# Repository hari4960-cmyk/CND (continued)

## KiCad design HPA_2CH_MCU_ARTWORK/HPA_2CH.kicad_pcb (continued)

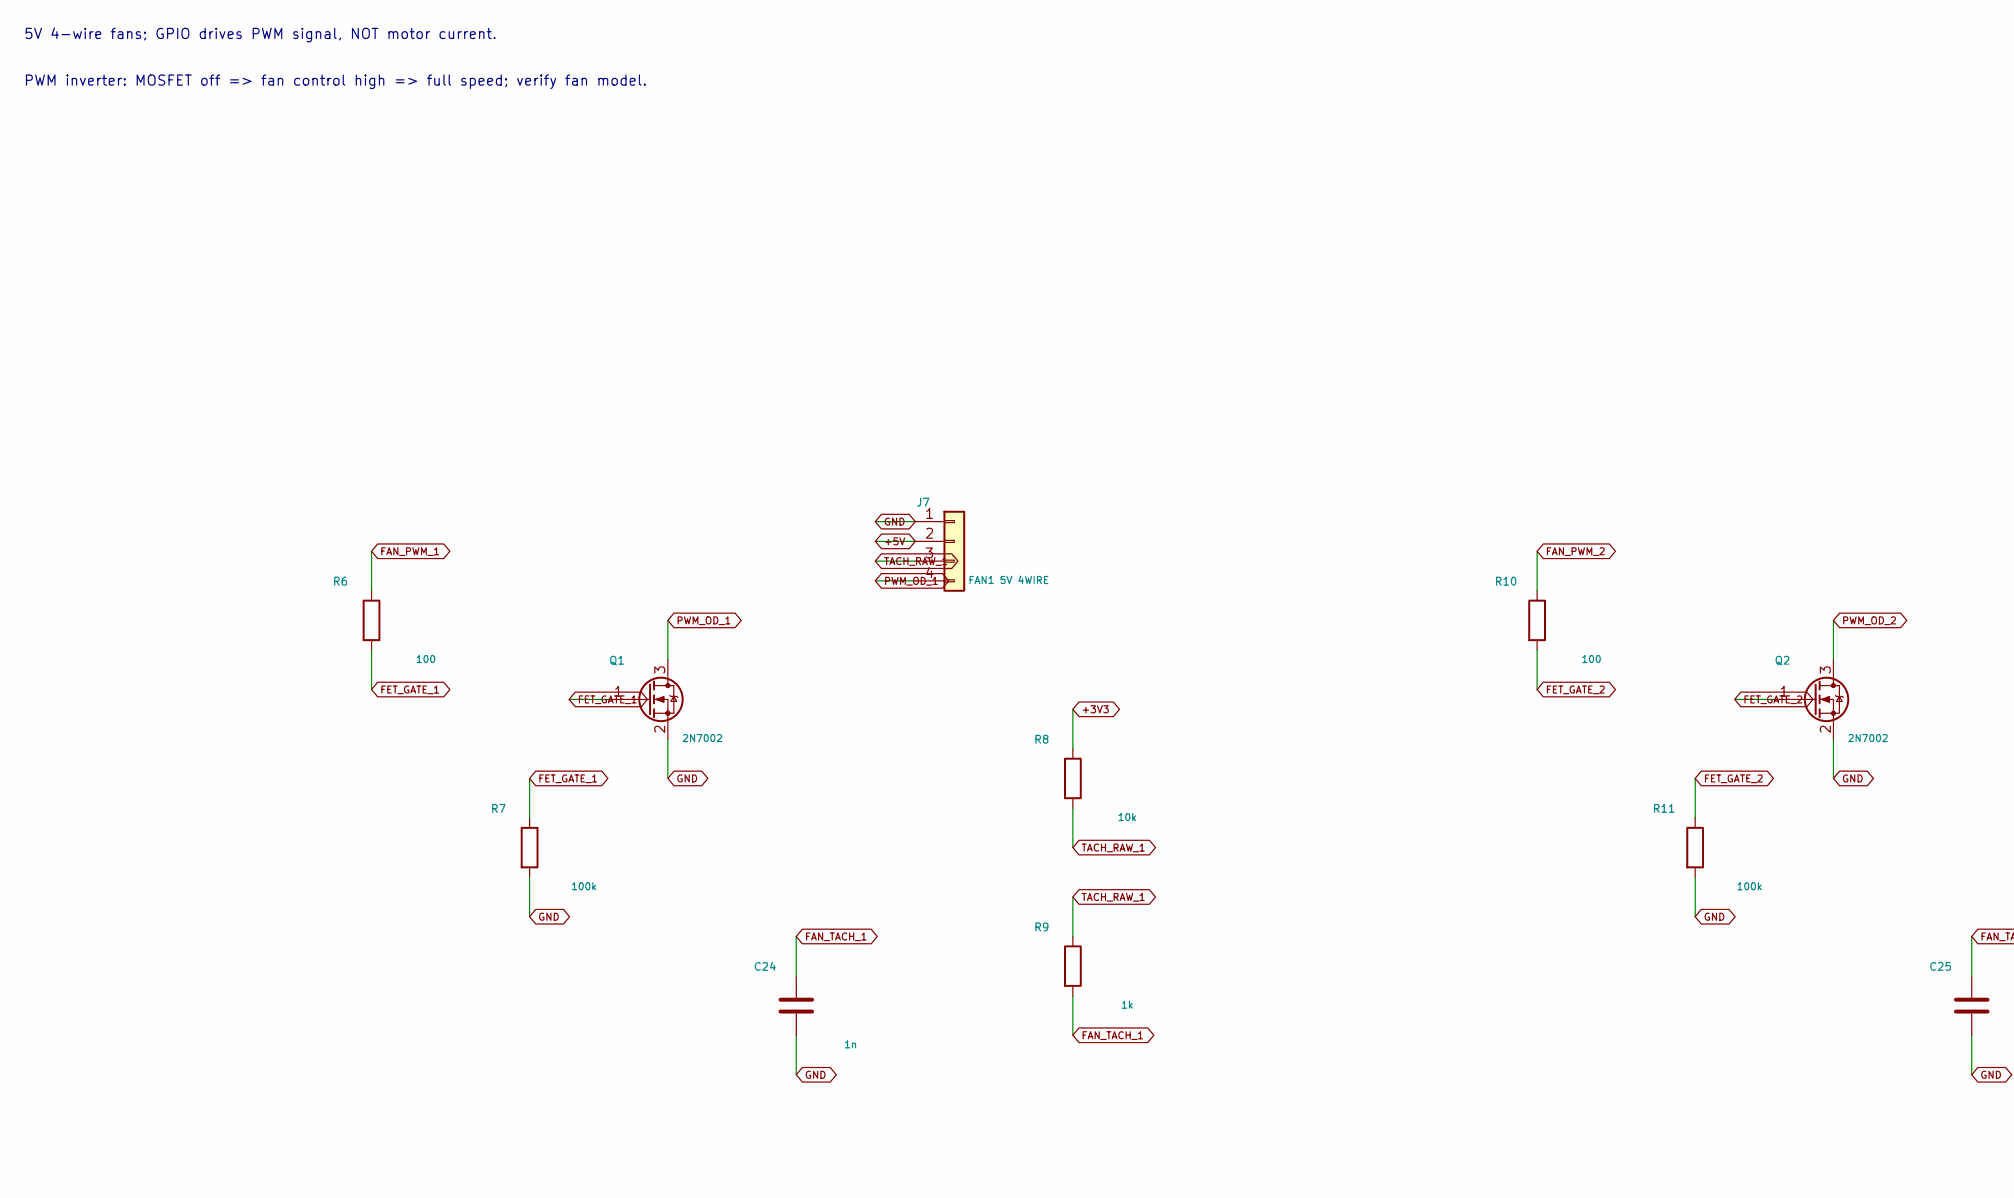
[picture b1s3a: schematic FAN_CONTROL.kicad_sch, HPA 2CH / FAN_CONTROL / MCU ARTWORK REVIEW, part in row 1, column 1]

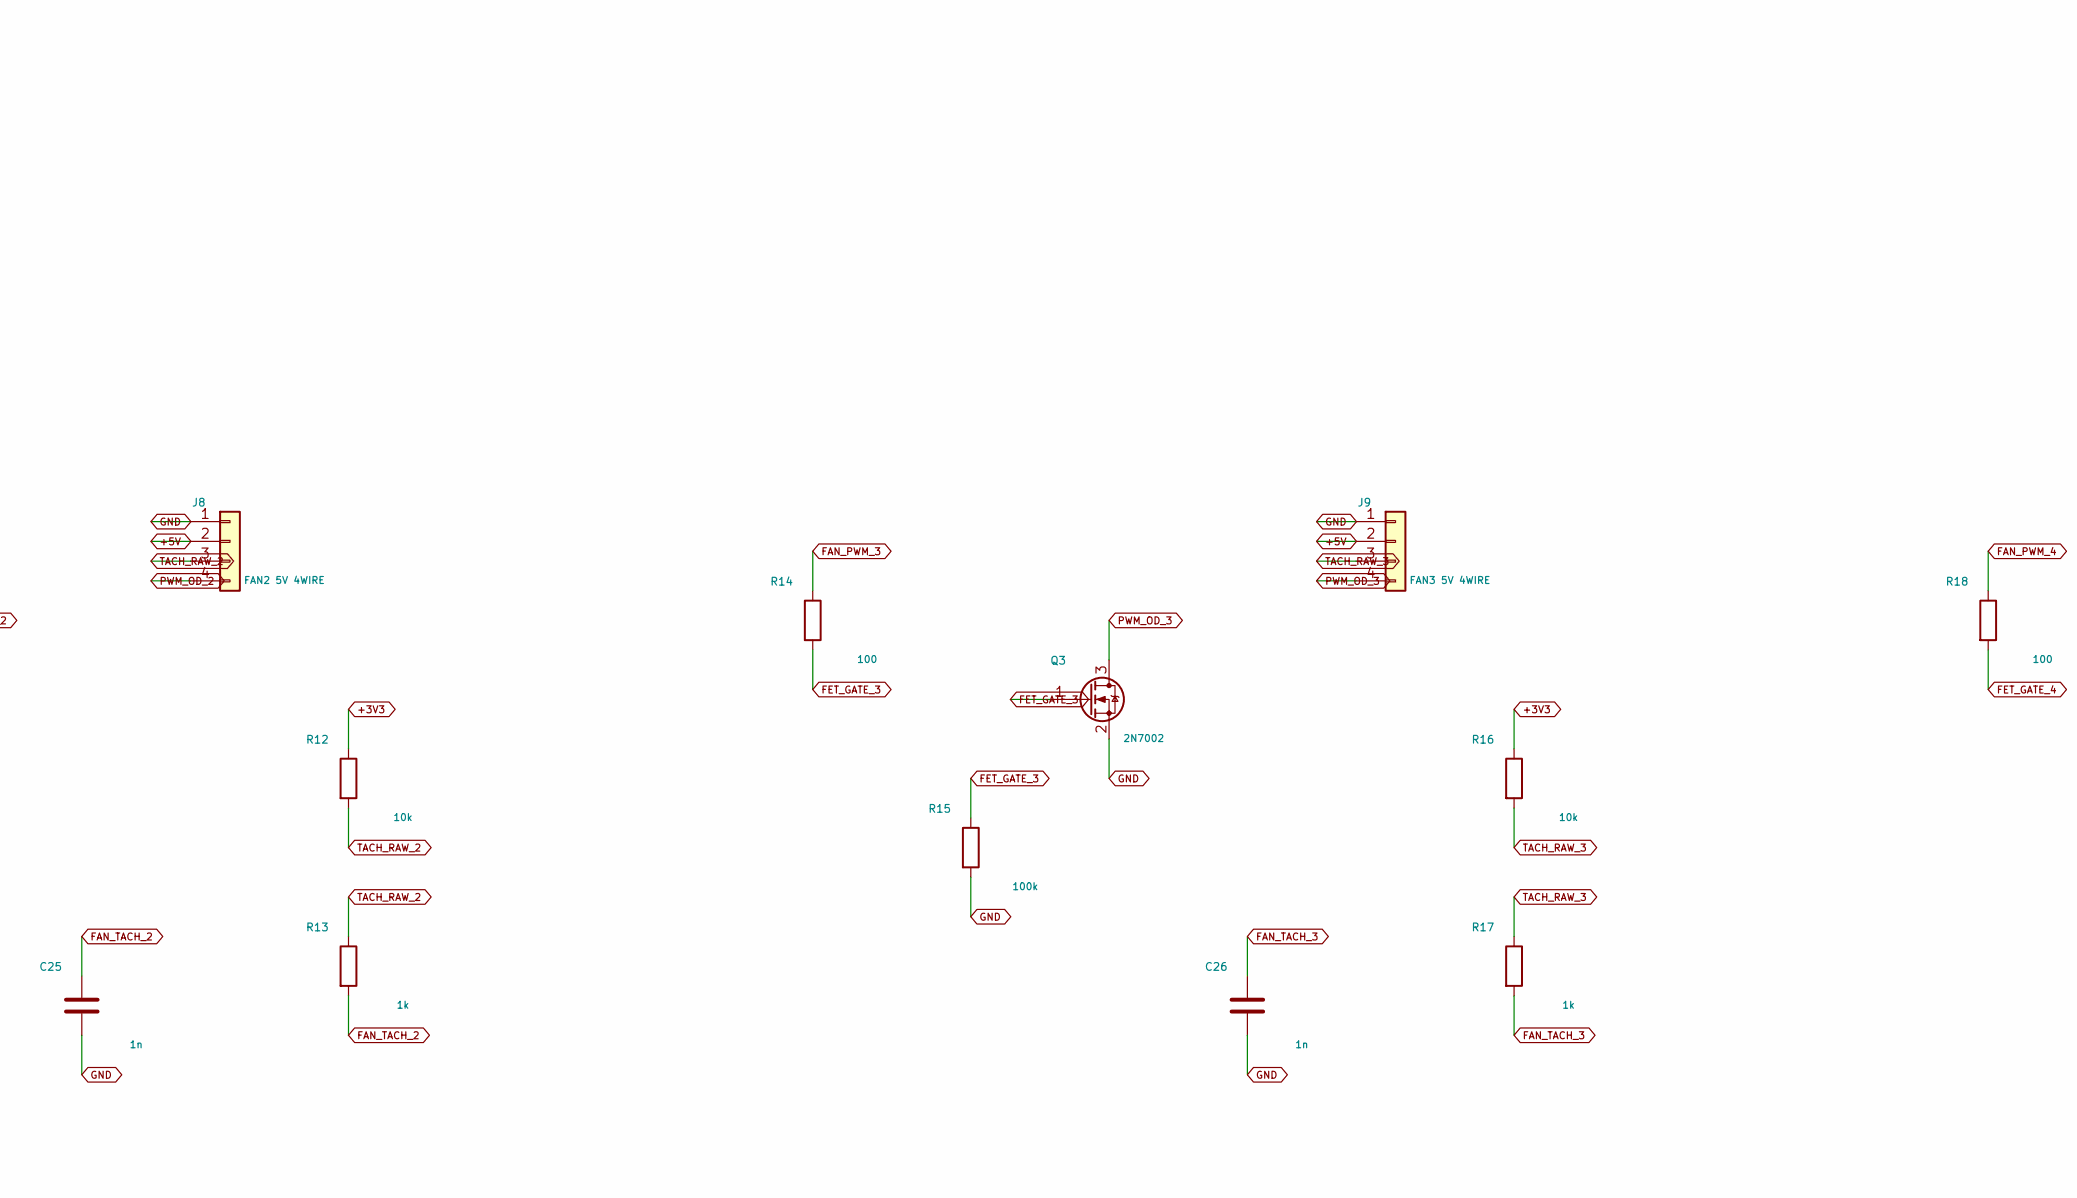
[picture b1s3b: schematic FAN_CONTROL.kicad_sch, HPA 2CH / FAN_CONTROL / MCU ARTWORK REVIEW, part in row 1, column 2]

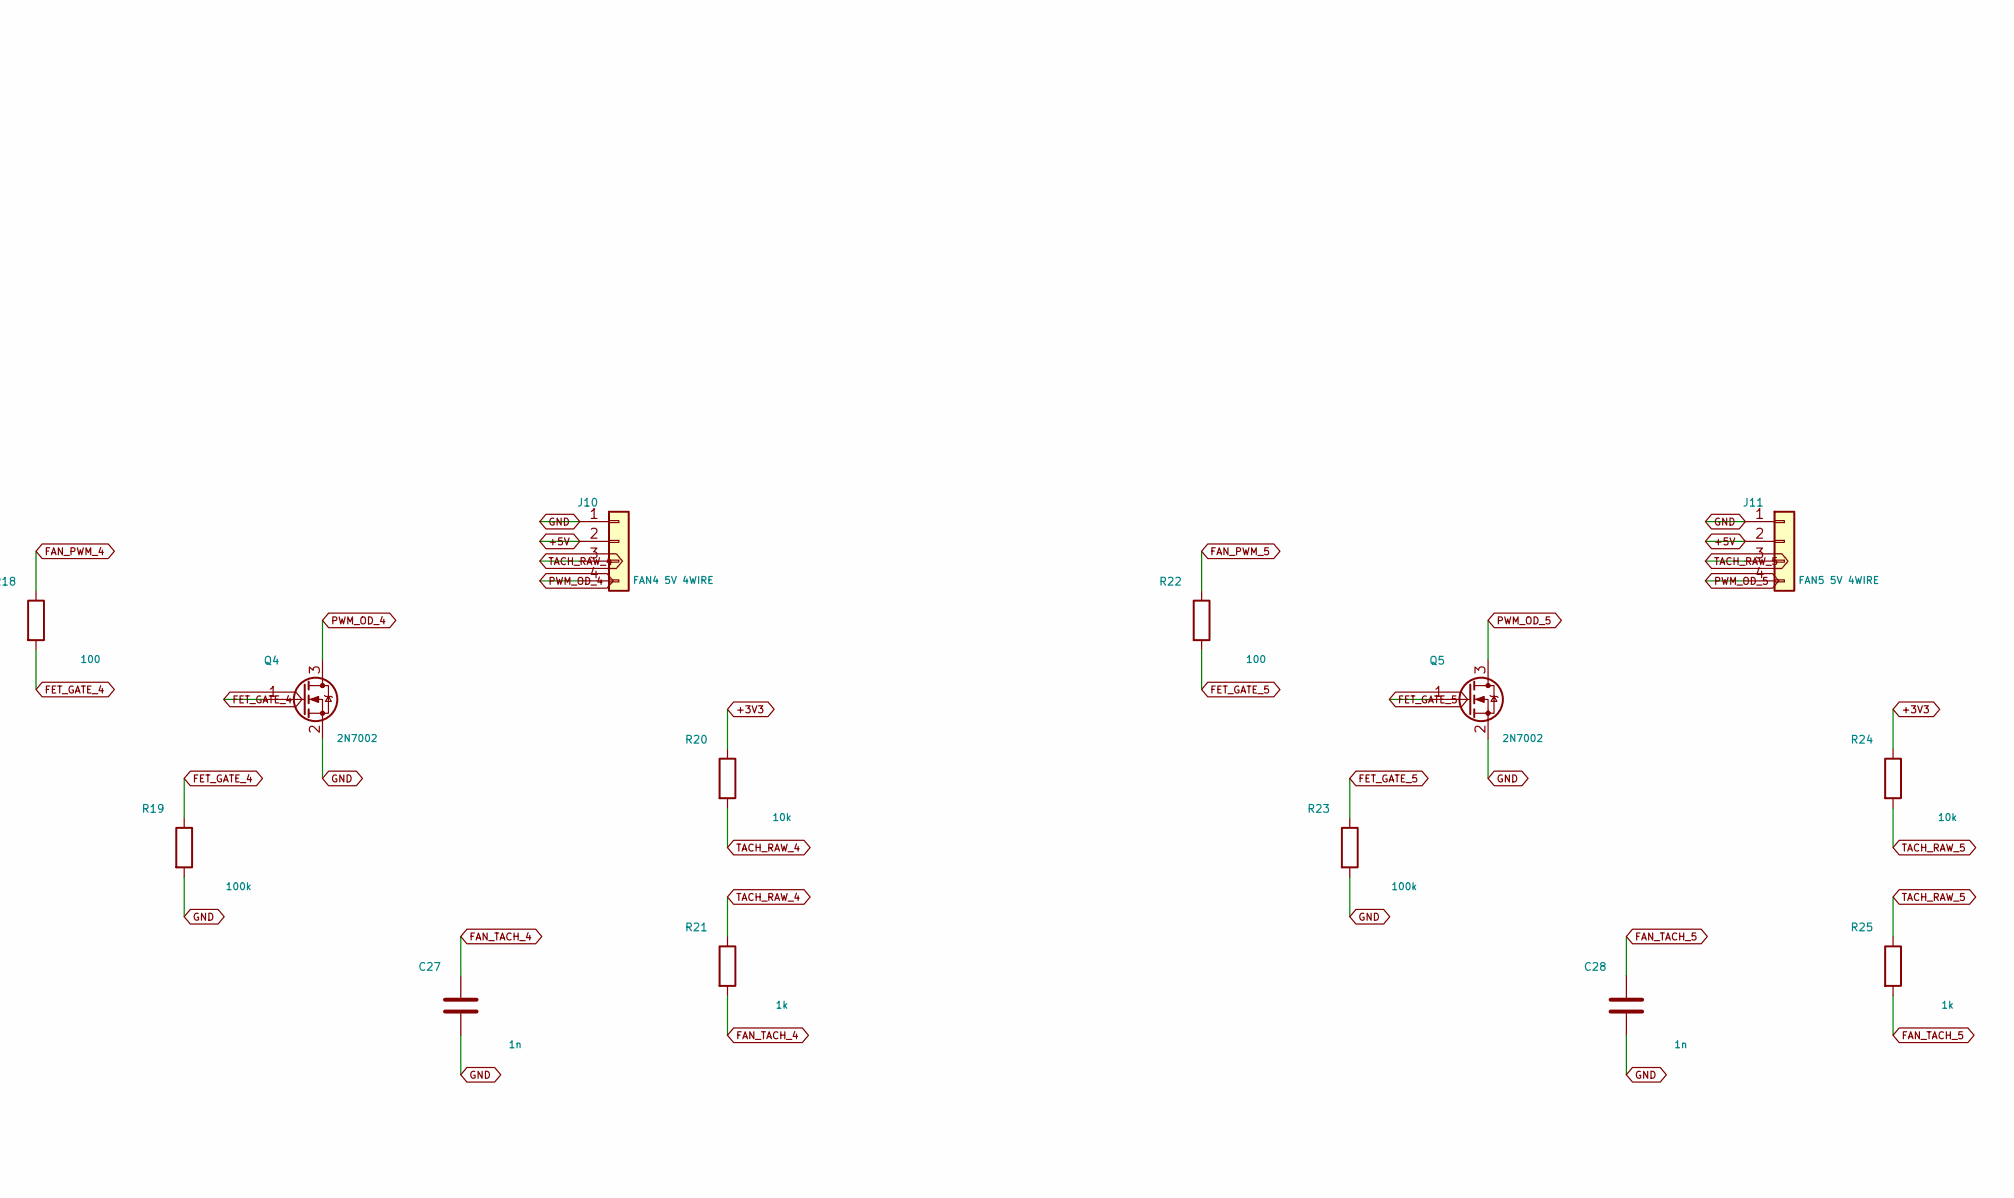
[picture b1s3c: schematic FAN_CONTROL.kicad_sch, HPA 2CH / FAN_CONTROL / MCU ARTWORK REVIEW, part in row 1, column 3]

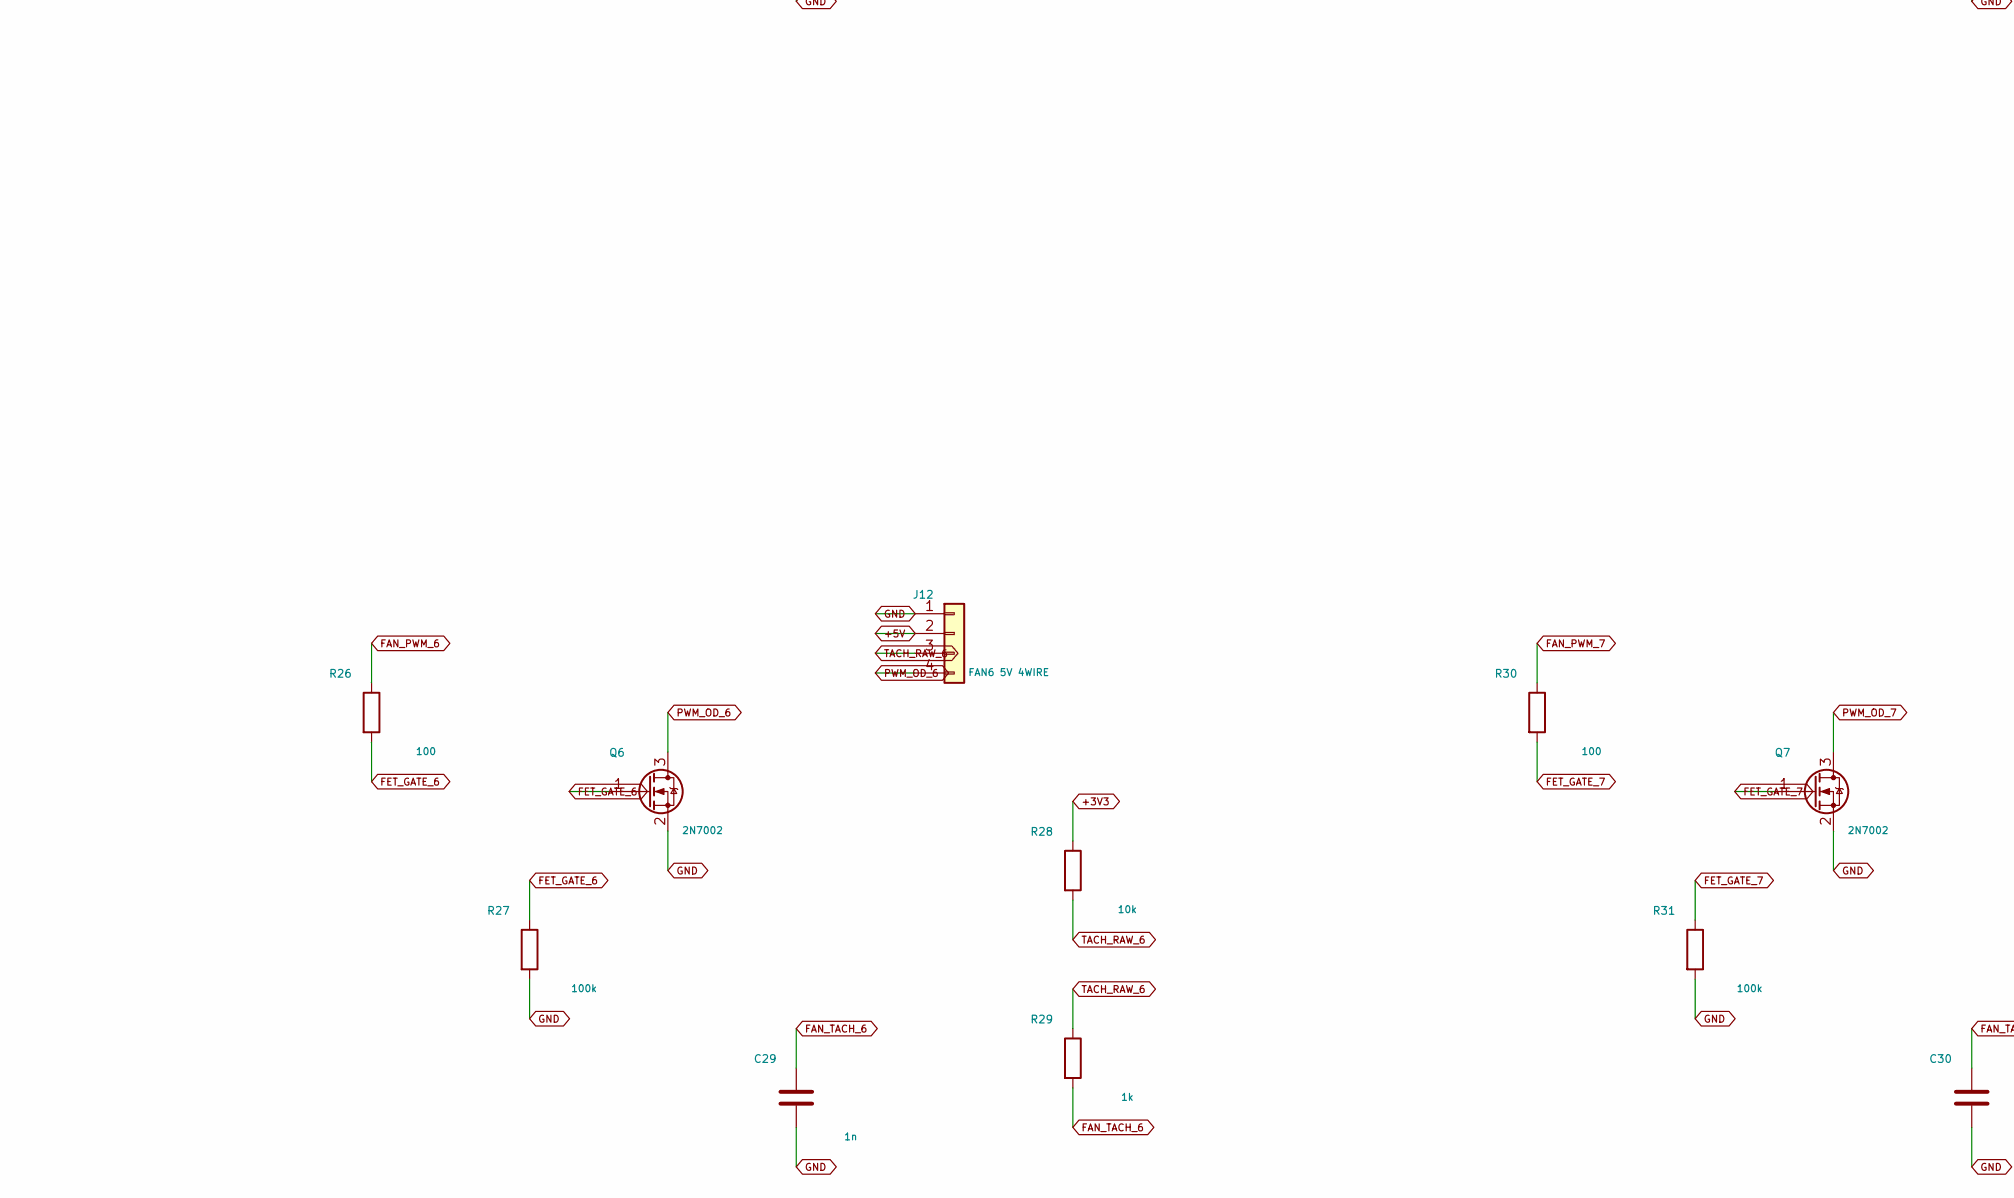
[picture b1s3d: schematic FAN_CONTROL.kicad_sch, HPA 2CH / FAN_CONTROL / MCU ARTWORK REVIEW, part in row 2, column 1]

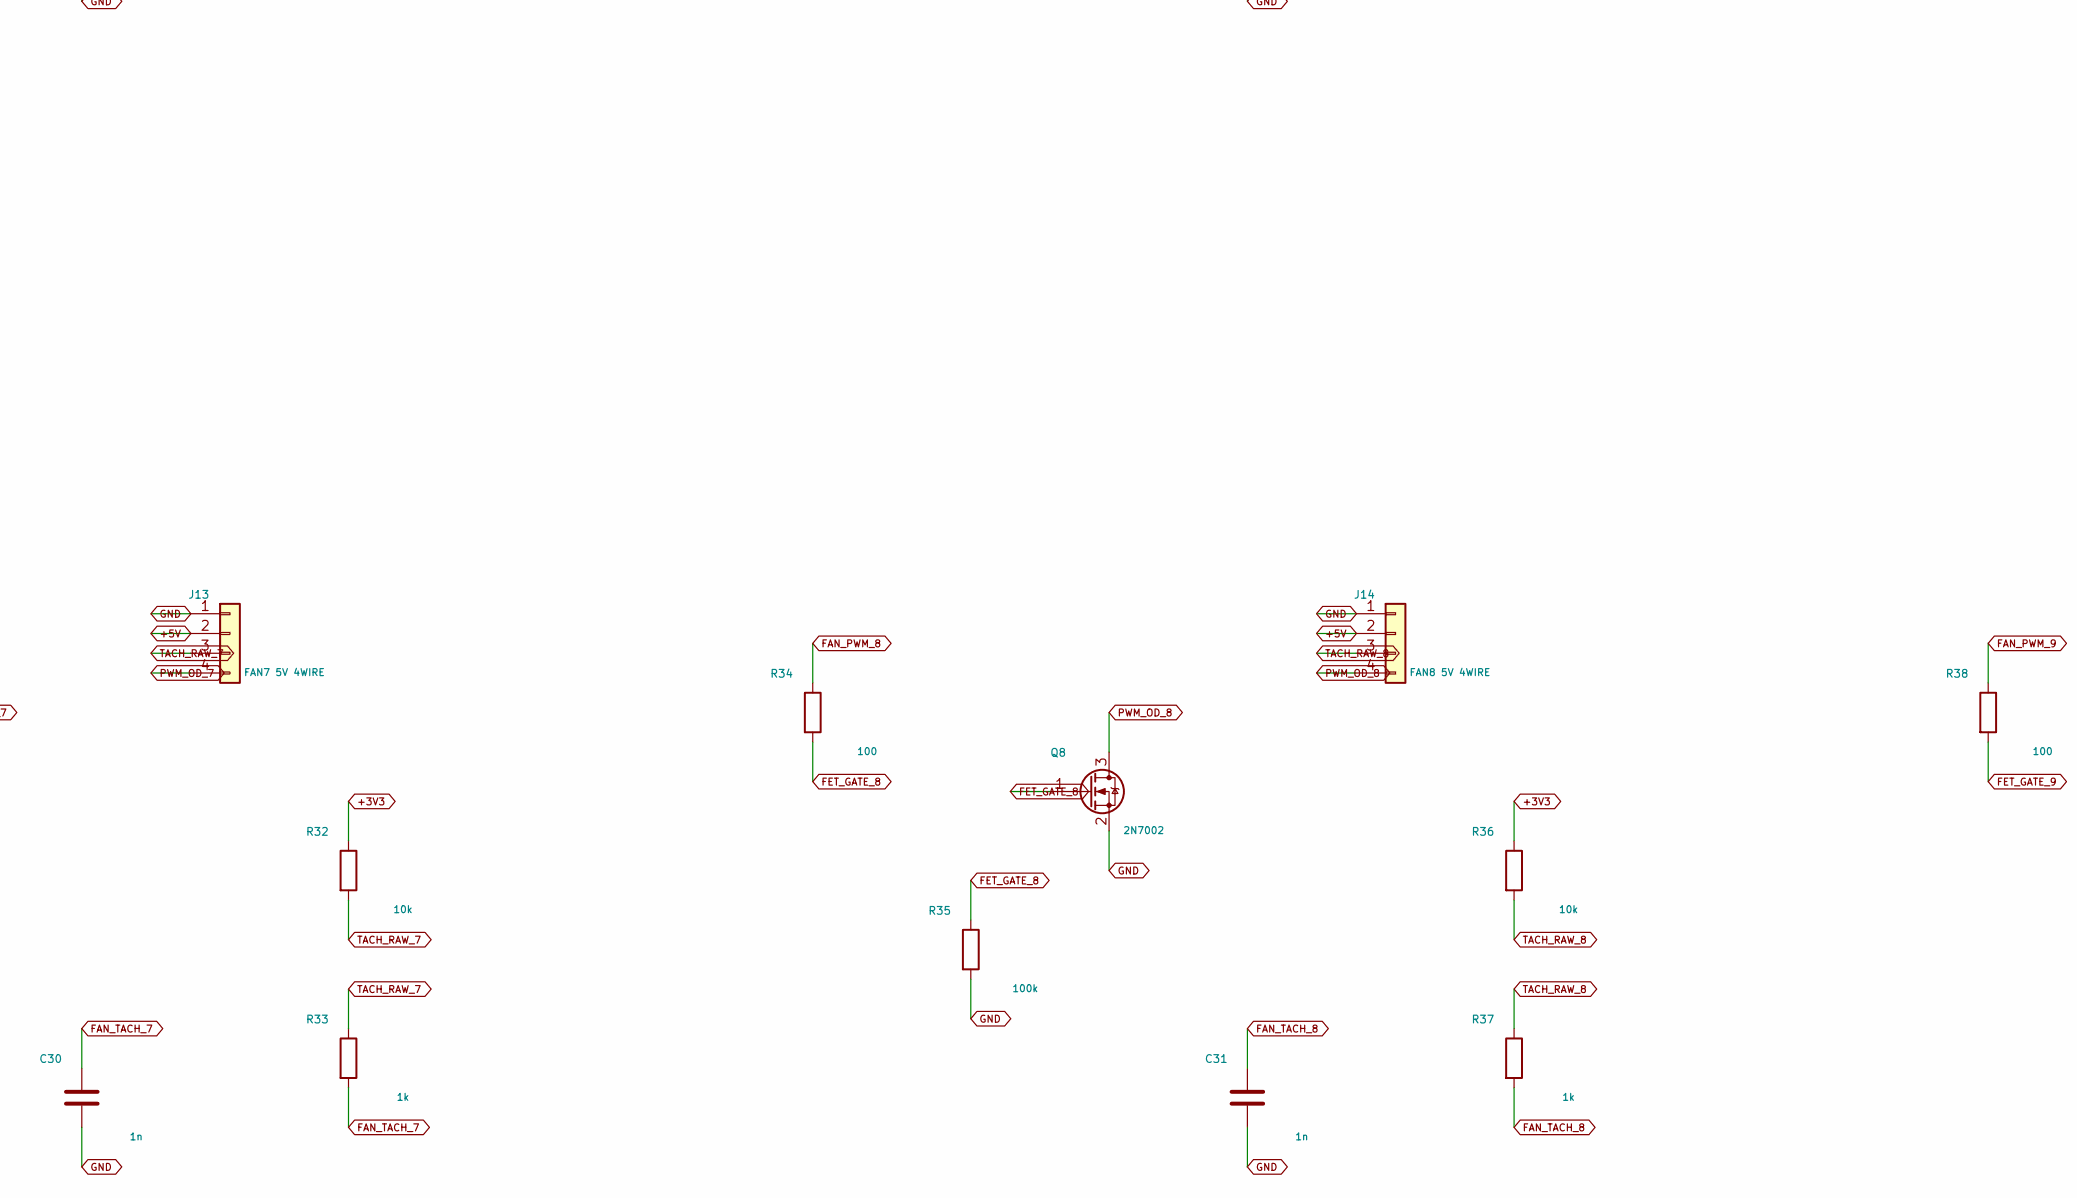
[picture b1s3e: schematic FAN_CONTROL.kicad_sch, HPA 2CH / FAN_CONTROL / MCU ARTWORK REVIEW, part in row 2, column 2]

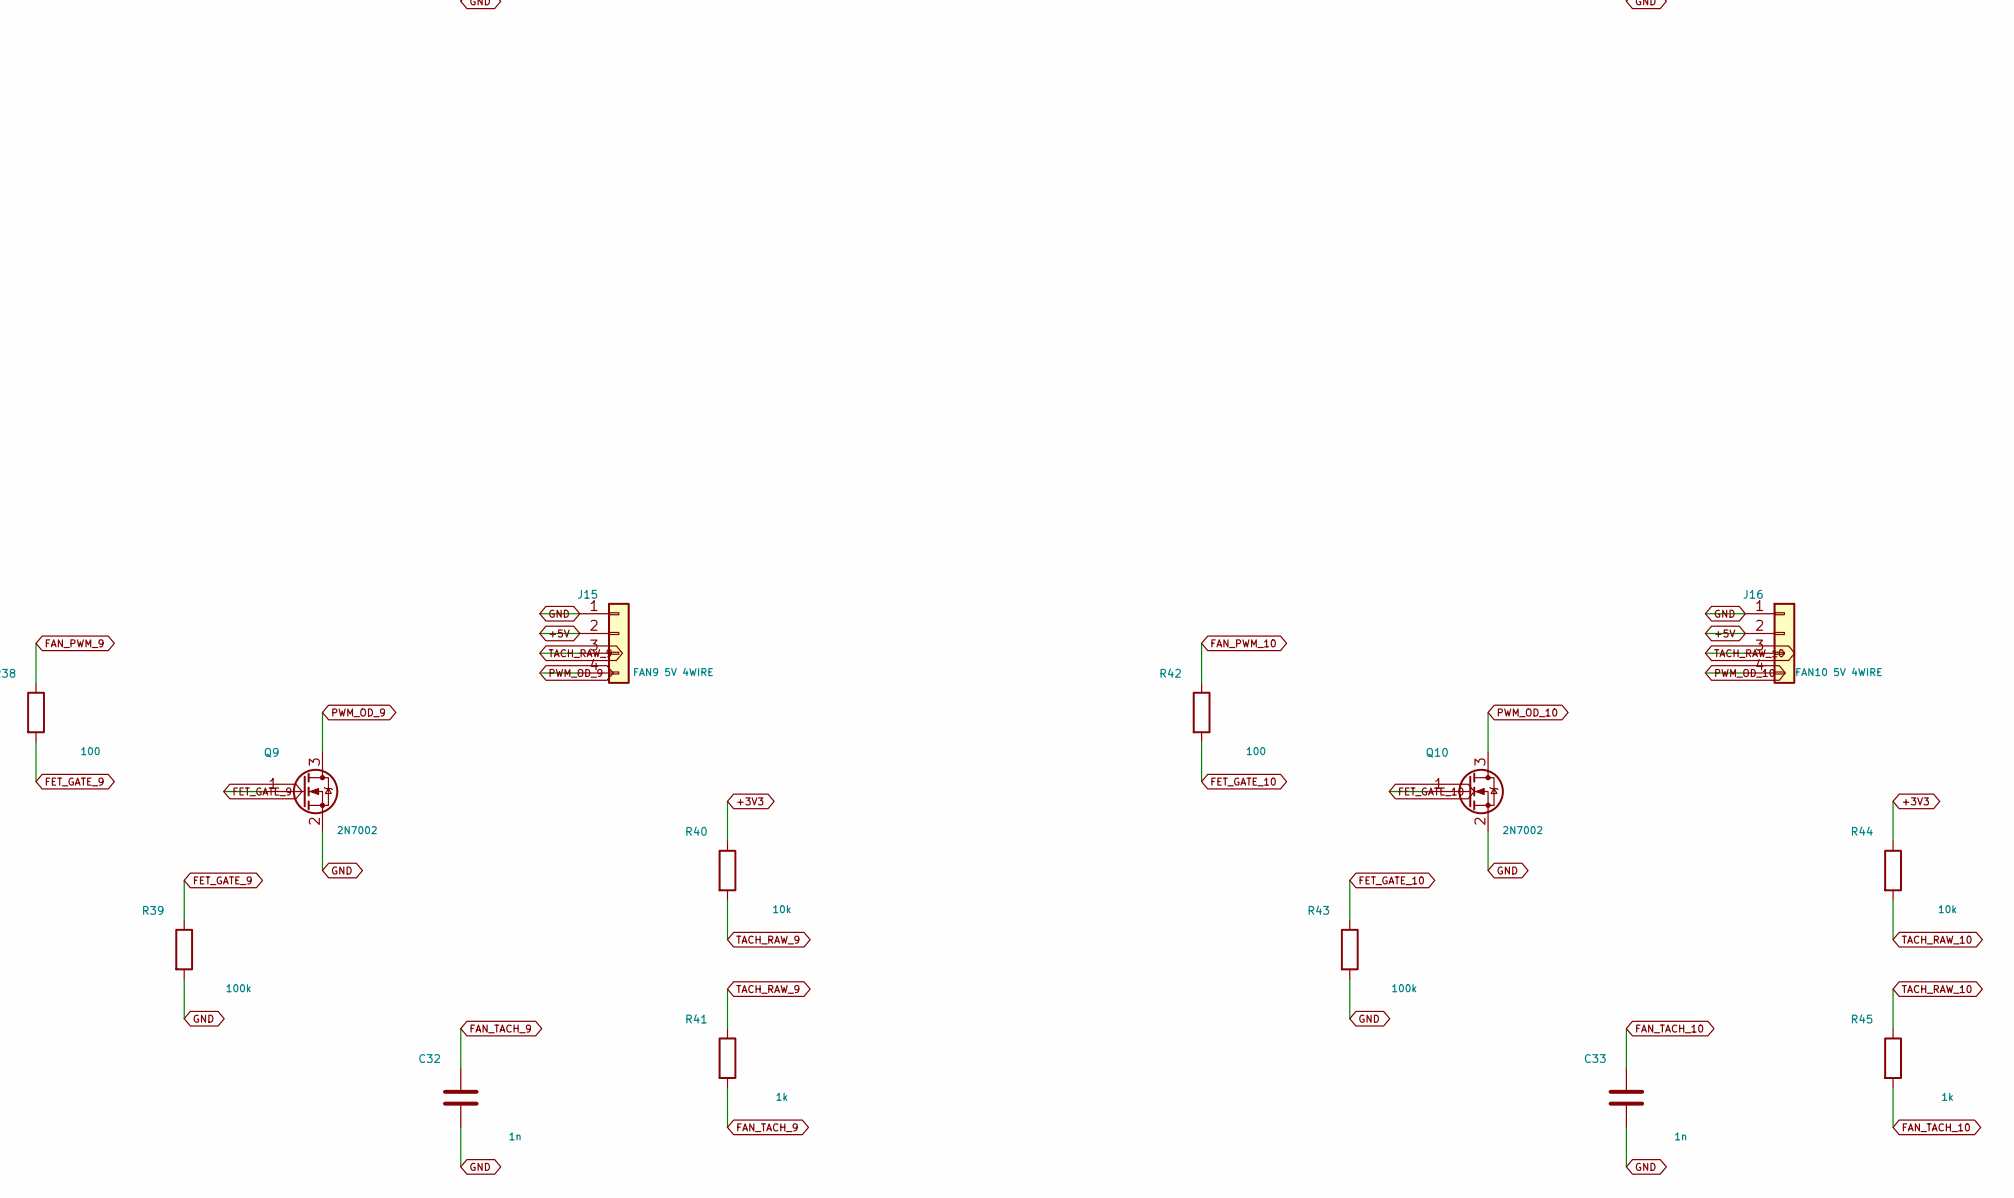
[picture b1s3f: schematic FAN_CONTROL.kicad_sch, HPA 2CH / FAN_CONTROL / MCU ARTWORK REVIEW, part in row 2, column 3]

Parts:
C24, C25, C26, C27, C28, C29, C30, C31, C32, C33: 1n; C_0603_1608Metric
J7: FAN1 5V 4WIRE; PinHeader_1x04_P2.54mm_Vertical
J8: FAN2 5V 4WIRE; PinHeader_1x04_P2.54mm_Vertical
J9: FAN3 5V 4WIRE; PinHeader_1x04_P2.54mm_Vertical
J10: FAN4 5V 4WIRE; PinHeader_1x04_P2.54mm_Vertical
J11: FAN5 5V 4WIRE; PinHeader_1x04_P2.54mm_Vertical
J12: FAN6 5V 4WIRE; PinHeader_1x04_P2.54mm_Vertical
J13: FAN7 5V 4WIRE; PinHeader_1x04_P2.54mm_Vertical
J14: FAN8 5V 4WIRE; PinHeader_1x04_P2.54mm_Vertical
J15: FAN9 5V 4WIRE; PinHeader_1x04_P2.54mm_Vertical
J16: FAN10 5V 4WIRE; PinHeader_1x04_P2.54mm_Vertical
Q1, Q2, Q3, Q4, Q5, Q6, Q7, Q8, Q9, Q10: 2N7002; SOT-23
R6, R10, R14, R18, R22, R26, R30, R34, R38, R42: 100; R_0603_1608Metric
R7, R11, R15, R19, R23, R27, R31, R35, R39, R43: 100k; R_0603_1608Metric
R8, R12, R16, R20, R24, R28, R32, R36, R40, R44: 10k; R_0603_1608Metric
R9, R13, R17, R21, R25, R29, R33, R37, R41, R45: 1k; R_0603_1608Metric

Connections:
+3V3: R8.1, R12.1, R16.1, R20.1, R24.1, R28.1, R32.1, R36.1, R40.1, R44.1; also elsewhere on the board
+5V: J7.2, J8.2, J9.2, J10.2, J11.2, J12.2, J13.2, J14.2, J15.2, J16.2; also elsewhere on the board
FAN_PWM_1: R6.1; also elsewhere on the board
FAN_PWM_2: R10.1; also elsewhere on the board
FAN_PWM_3: R14.1; also elsewhere on the board
FAN_PWM_4: R18.1; also elsewhere on the board
FAN_PWM_5: R22.1; also elsewhere on the board
FAN_PWM_6: R26.1; also elsewhere on the board
FAN_PWM_7: R30.1; also elsewhere on the board
FAN_PWM_8: R34.1; also elsewhere on the board
FAN_PWM_9: R38.1; also elsewhere on the board
FAN_PWM_10: R42.1; also elsewhere on the board
FAN_TACH_1: C24.1, R9.2; also elsewhere on the board
FAN_TACH_2: C25.1, R13.2; also elsewhere on the board
FAN_TACH_3: C26.1, R17.2; also elsewhere on the board
FAN_TACH_4: C27.1, R21.2; also elsewhere on the board
FAN_TACH_5: C28.1, R25.2; also elsewhere on the board
FAN_TACH_6: C29.1, R29.2; also elsewhere on the board
FAN_TACH_7: C30.1, R33.2; also elsewhere on the board
FAN_TACH_8: C31.1, R37.2; also elsewhere on the board
FAN_TACH_9: C32.1, R41.2; also elsewhere on the board
FAN_TACH_10: C33.1, R45.2; also elsewhere on the board
FET_GATE_1: Q1.1 (G), R6.2, R7.1
FET_GATE_2: Q2.1 (G), R10.2, R11.1
FET_GATE_3: Q3.1 (G), R14.2, R15.1
FET_GATE_4: Q4.1 (G), R18.2, R19.1
FET_GATE_5: Q5.1 (G), R22.2, R23.1
FET_GATE_6: Q6.1 (G), R26.2, R27.1
FET_GATE_7: Q7.1 (G), R30.2, R31.1
FET_GATE_8: Q8.1 (G), R34.2, R35.1
FET_GATE_9: Q9.1 (G), R38.2, R39.1
FET_GATE_10: Q10.1 (G), R42.2, R43.1
GND: C24.2, C25.2, C26.2, C27.2, C28.2, C29.2, C30.2, C31.2, C32.2, C33.2, J7.1, J8.1, J9.1, J10.1, J11.1, J12.1, J13.1, J14.1, J15.1, J16.1, Q1.2 (S), Q2.2 (S), Q3.2 (S), Q4.2 (S), Q5.2 (S), Q6.2 (S), Q7.2 (S), Q8.2 (S), Q9.2 (S), Q10.2 (S), R7.2, R11.2, R15.2, R19.2, R23.2, R27.2, R31.2, R35.2, R39.2, R43.2; also elsewhere on the board
PWM_OD_1: J7.4, Q1.3 (D)
PWM_OD_2: J8.4, Q2.3 (D)
PWM_OD_3: J9.4, Q3.3 (D)
PWM_OD_4: J10.4, Q4.3 (D)
PWM_OD_5: J11.4, Q5.3 (D)
PWM_OD_6: J12.4, Q6.3 (D)
PWM_OD_7: J13.4, Q7.3 (D)
PWM_OD_8: J14.4, Q8.3 (D)
PWM_OD_9: J15.4, Q9.3 (D)
PWM_OD_10: J16.4, Q10.3 (D)
TACH_RAW_1: J7.3, R8.2, R9.1
TACH_RAW_2: J8.3, R12.2, R13.1
TACH_RAW_3: J9.3, R16.2, R17.1
TACH_RAW_4: J10.3, R20.2, R21.1
TACH_RAW_5: J11.3, R24.2, R25.1
TACH_RAW_6: J12.3, R28.2, R29.1
TACH_RAW_7: J13.3, R32.2, R33.1
TACH_RAW_8: J14.3, R36.2, R37.1
TACH_RAW_9: J15.3, R40.2, R41.1
TACH_RAW_10: J16.3, R44.2, R45.1

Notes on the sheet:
5V 4-wire fans; GPIO drives PWM signal, NOT motor current.
PWM inverter: MOSFET off => fan control high => full speed; verify fan model.

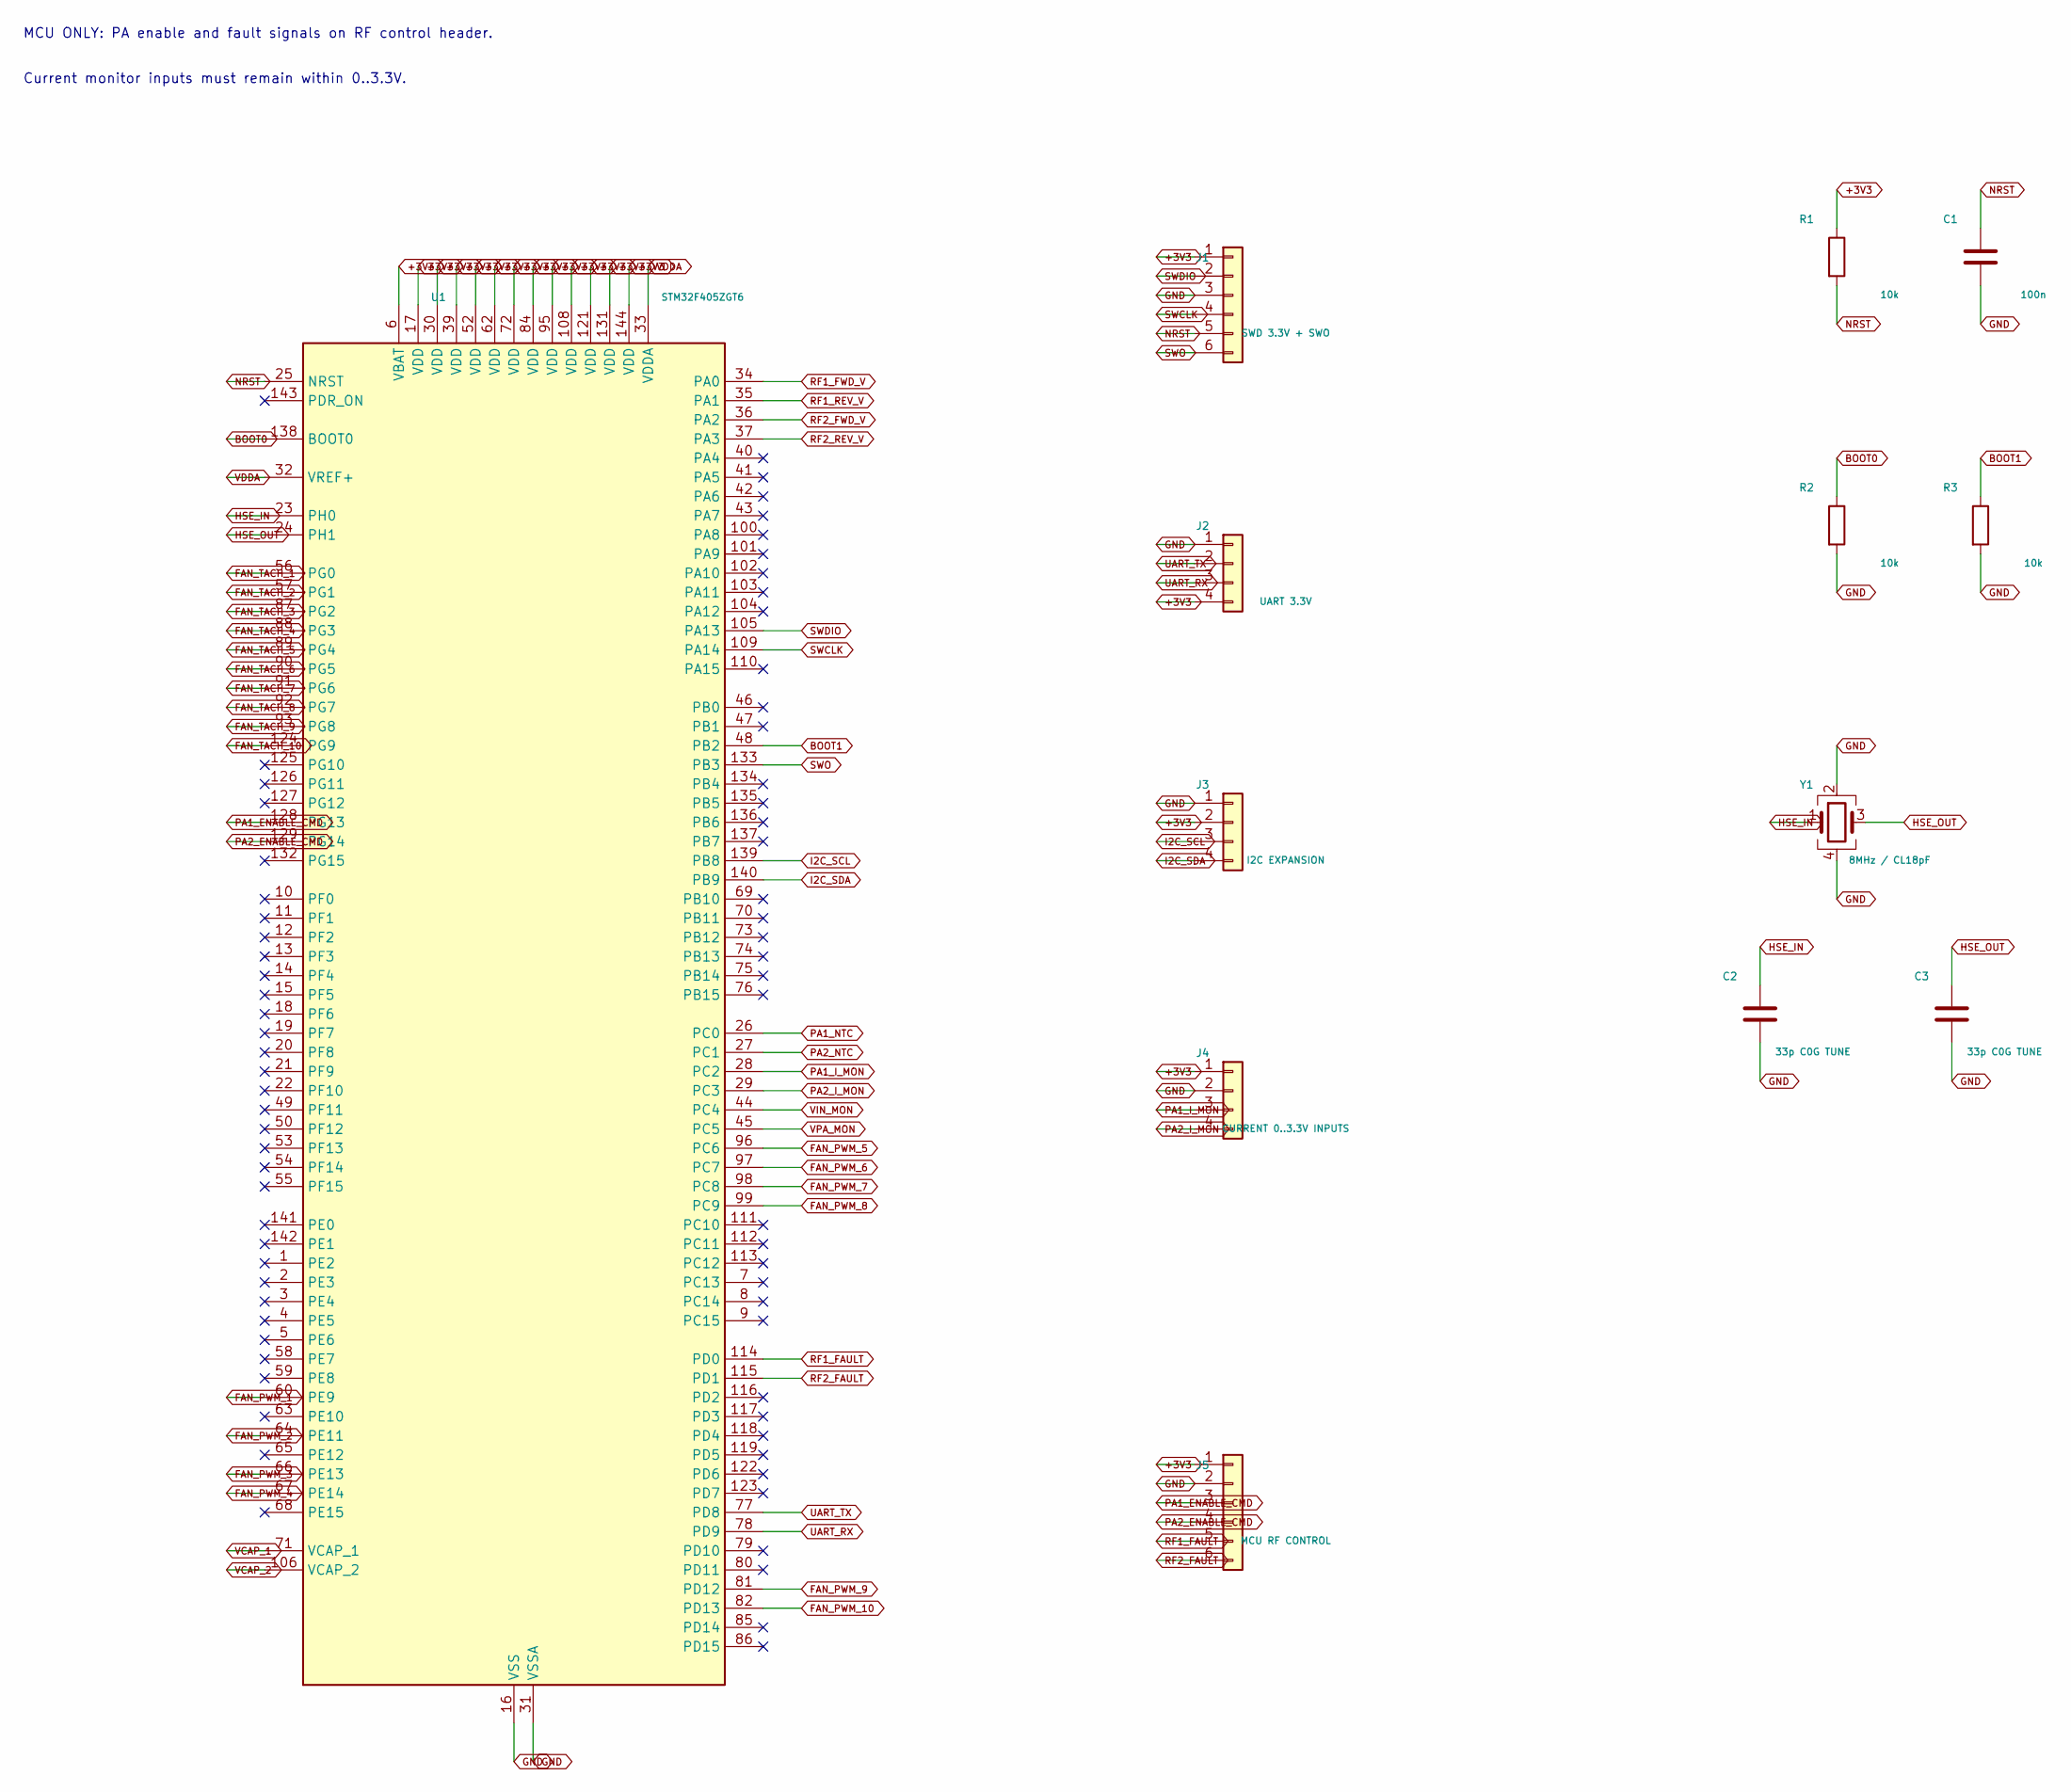
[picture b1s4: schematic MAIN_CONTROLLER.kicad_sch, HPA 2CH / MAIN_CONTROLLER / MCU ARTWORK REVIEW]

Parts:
C1: 100n; C_0603_1608Metric
C2, C3: 33p C0G TUNE; C_0603_1608Metric
J1: SWD 3.3V + SWO; PinHeader_1x06_P2.54mm_Vertical
J2: UART 3.3V; PinHeader_1x04_P2.54mm_Vertical
J3: I2C EXPANSION; PinHeader_1x04_P2.54mm_Vertical
J4: CURRENT 0..3.3V INPUTS; PinHeader_1x04_P2.54mm_Vertical
J5: MCU RF CONTROL; PinHeader_1x06_P2.54mm_Vertical
R1, R2, R3: 10k; R_0603_1608Metric
U1: STM32F405ZGT6; LQFP-144_20x20mm_P0.5mm
Y1: 8MHz / CL18pF; Crystal_SMD_3225-4Pin_3.2x2.5mm

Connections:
+3V3: J1.1, J2.4, J3.2, J4.1, J5.1, R1.1, U1.6 (VBAT), U1.17 (VDD), U1.30 (VDD), U1.39 (VDD), U1.52 (VDD), U1.62 (VDD), U1.72 (VDD), U1.84 (VDD), U1.95 (VDD), U1.108 (VDD), U1.121 (VDD), U1.131 (VDD), U1.144 (VDD); also elsewhere on the board
BOOT0: R2.1, U1.138 (BOOT0)
BOOT1: R3.1, U1.48 (PB2)
FAN_PWM_1: U1.60 (PE9); also elsewhere on the board
FAN_PWM_2: U1.64 (PE11); also elsewhere on the board
FAN_PWM_3: U1.66 (PE13); also elsewhere on the board
FAN_PWM_4: U1.67 (PE14); also elsewhere on the board
FAN_PWM_5: U1.96 (PC6); also elsewhere on the board
FAN_PWM_6: U1.97 (PC7); also elsewhere on the board
FAN_PWM_7: U1.98 (PC8); also elsewhere on the board
FAN_PWM_8: U1.99 (PC9); also elsewhere on the board
FAN_PWM_9: U1.81 (PD12); also elsewhere on the board
FAN_PWM_10: U1.82 (PD13); also elsewhere on the board
FAN_TACH_1: U1.56 (PG0); also elsewhere on the board
FAN_TACH_2: U1.57 (PG1); also elsewhere on the board
FAN_TACH_3: U1.87 (PG2); also elsewhere on the board
FAN_TACH_4: U1.88 (PG3); also elsewhere on the board
FAN_TACH_5: U1.89 (PG4); also elsewhere on the board
FAN_TACH_6: U1.90 (PG5); also elsewhere on the board
FAN_TACH_7: U1.91 (PG6); also elsewhere on the board
FAN_TACH_8: U1.92 (PG7); also elsewhere on the board
FAN_TACH_9: U1.93 (PG8); also elsewhere on the board
FAN_TACH_10: U1.124 (PG9); also elsewhere on the board
GND: C1.2, C2.2, C3.2, J1.3, J2.1, J3.1, J4.2, J5.2, R2.2, R3.2, U1.16 (VSS), U1.31 (VSSA), U1.38 (VSS), U1.51 (VSS), U1.61 (VSS), U1.83 (VSS), U1.94 (VSS), U1.107 (VSS), U1.120 (VSS), U1.130 (VSS), Y1.2, Y1.4; also elsewhere on the board
HSE_IN: C2.1, U1.23 (PH0), Y1.1
HSE_OUT: C3.1, U1.24 (PH1), Y1.3
I2C_SCL: J3.3, U1.139 (PB8)
I2C_SDA: J3.4, U1.140 (PB9)
NRST: C1.1, J1.5, R1.2, U1.25 (NRST)
PA1_ENABLE_CMD: J5.3, U1.128 (PG13)
PA1_I_MON: J4.3, U1.28 (PC2)
PA1_NTC: U1.26 (PC0); also elsewhere on the board
PA2_ENABLE_CMD: J5.4, U1.129 (PG14)
PA2_I_MON: J4.4, U1.29 (PC3)
PA2_NTC: U1.27 (PC1); also elsewhere on the board
RF1_FAULT: J5.5, U1.114 (PD0)
RF1_FWD_V: U1.34 (PA0); also elsewhere on the board
RF1_REV_V: U1.35 (PA1); also elsewhere on the board
RF2_FAULT: J5.6, U1.115 (PD1)
RF2_FWD_V: U1.36 (PA2); also elsewhere on the board
RF2_REV_V: U1.37 (PA3); also elsewhere on the board
SWCLK: J1.4, U1.109 (PA14)
SWDIO: J1.2, U1.105 (PA13)
SWO: J1.6, U1.133 (PB3)
UART_RX: J2.3, U1.78 (PD9)
UART_TX: J2.2, U1.77 (PD8)
VCAP_1: U1.71 (VCAP_1); also elsewhere on the board
VCAP_2: U1.106 (VCAP_2); also elsewhere on the board
VDDA: U1.32 (VREF+), U1.33 (VDDA); also elsewhere on the board
VIN_MON: U1.44 (PC4); also elsewhere on the board
VPA_MON: U1.45 (PC5); also elsewhere on the board

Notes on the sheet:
MCU ONLY: PA enable and fault signals on RF control header.
Current monitor inputs must remain within 0..3.3V.
